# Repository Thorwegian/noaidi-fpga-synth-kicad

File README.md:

# Noaidi FPGA Synth: the board

The KiCad project for the Noaidi synthesizer's circuit board, in
progress. The gateware and firmware that run on it live in
[Thorwegian/noaidi-fpga-synth](https://github.com/Thorwegian/noaidi-fpga-synth),
and the synth itself is presented at [thj.no/synth](https://thj.no/synth/).

## What is on it

The perfboard prototype the board is based on. The board is a carrier for
two off-the-shelf modules and the few parts around them:

- **Tang Nano 20K** (U2) on headers: the sound engine.
- **ESP32-S3-DevKitC** (U1) on headers: MIDI, voices, patches and the
  console. The prototype runs an ESP32-C3 Super Mini; the board moves to
  the S3 (the firmware port is tracked in the synth repository,
  `docs/esp32s3_hw678.md`).
- **Two DIN MIDI inputs** (J1, J2) through 6N138 optocouplers (U3, U4):
  one for the keyboard, one for the dev host.
- **Audio out**: an Adafruit PCM510x I2S DAC module (U5) for analog, two
  RCA sockets (J3, J4) for S/PDIF.
- **USB-C** (J9) for power, into each module's 5 V rail through an
  LM66100 ideal diode (U6, U7), and the data pair to the ESP32.
- Pin headers for the second SPI bus, two I2C buses, UART0, I2S and
  S/PDIF, and 29 test points.

Two layers, 130.85 × 121.25 mm, through-hole apart from the two LM66100
(SC-70) and the ferrite bead.

## Layout

Front copper and silkscreen:

Back copper, mirrored:

The connector and module bodies render as footprints only: their 3D
models are not part of the project.

## Schematic

[pcb-schematic.pdf](https://thj.no/synth/images/pcb-schematic.pdf), all
five sheets: the root, `esp32`, `tang_nano_20k`, `usb` and `test_points`.

## Files

The root folder holds the KiCad project, this README and the licence.
Scripts go in `scripts/`, documents in `docs/`.

- `noaidi-fpga-synth.kicad_pro`, `.kicad_sch` and the four sheet files,
  `.kicad_pcb`, `.kicad_dru`
- `noaidi-fpga-synth.kicad_sym` and `noaidi-fpga-synth.pretty/`: the
  project's own symbols and footprints (the two modules, the DAC, the
  DIN sockets, the RCA and USB-C connectors)
- `scripts/render.sh`: regenerates the images above into `build/` with
  `kicad-cli` (KiCad 10); `scripts/crop.py` trims the 3D renders to the
  board
- `docs/requirements.md`: what the board has to do; the schematic and
  the layout are checked against it.
- `docs/esp32s3_hw678.md`: what the two HW-678 copies of the
  ESP32-S3-DevKitC-1 are, measured: the pins the module takes, the
  free pins, the USB bridge and the open USB-OTG pads, and the header
  pins read from two photos of the board, `docs/esp32s3_hw678_top.jpg`
  and `docs/esp32s3_hw678_bottom.jpg`. The synth repository's file with
  the Header pins section added.
- `docs/thirdparty/`: the vendors' documents the board is drawn from.
  Mechanical: the Tang Nano 20K's dimension drawing (`.pdf`, `.dxf`) and
  3D model (`.step`), and the Adafruit PCM510x's fab print with its
  dimensions. Electrical: the Tang Nano 20K's schematic and pinout, the
  GW2AR data sheet, the ESP32-S3-DevKitC-1 user guide, pinouts and
  schematic (v1.1), the
  Adafruit PCM510x guide and schematic, the 6N138 MIDI input circuit and
  the TOTX1950A optical transmitter's data sheet. The board's own parts,
  from the links in the schematic's Datasheet fields: the LM66100 ideal
  diode (U6, U7), the 6N138 optocoupler (U3, U4), the Lumberg 0105 DIN
  socket (J1, J2), the Kycon KLPX RCA socket (J3, J4) and the GCT
  USB4085 USB-C receptacle (J9; specification and drawing).

## Build tools

`kicad-cli` (KiCad 10) and `pdfunite` (poppler-utils) come from the
system's packages. The Python tools are listed in
`scripts/requirements.txt` and live in a virtual environment, `.venv/`
at the root, which is not committed:

    python3 -m venv .venv
    .venv/bin/pip install -r scripts/requirements.txt
    source .venv/bin/activate

- `skidl`: circuits described in Python. It is not in Ubuntu's packages.
  It finds KiCad's symbol libraries through the environment variable
  `KICAD10_SYMBOL_DIR` (`/usr/share/kicad/symbols` on Ubuntu).
- `pillow`: for `scripts/crop.py`.

Copyright © 2026 Thor H. Linløkken <thj@thj.no>
License: [CERN-OHL-S v2](LICENSE.txt)

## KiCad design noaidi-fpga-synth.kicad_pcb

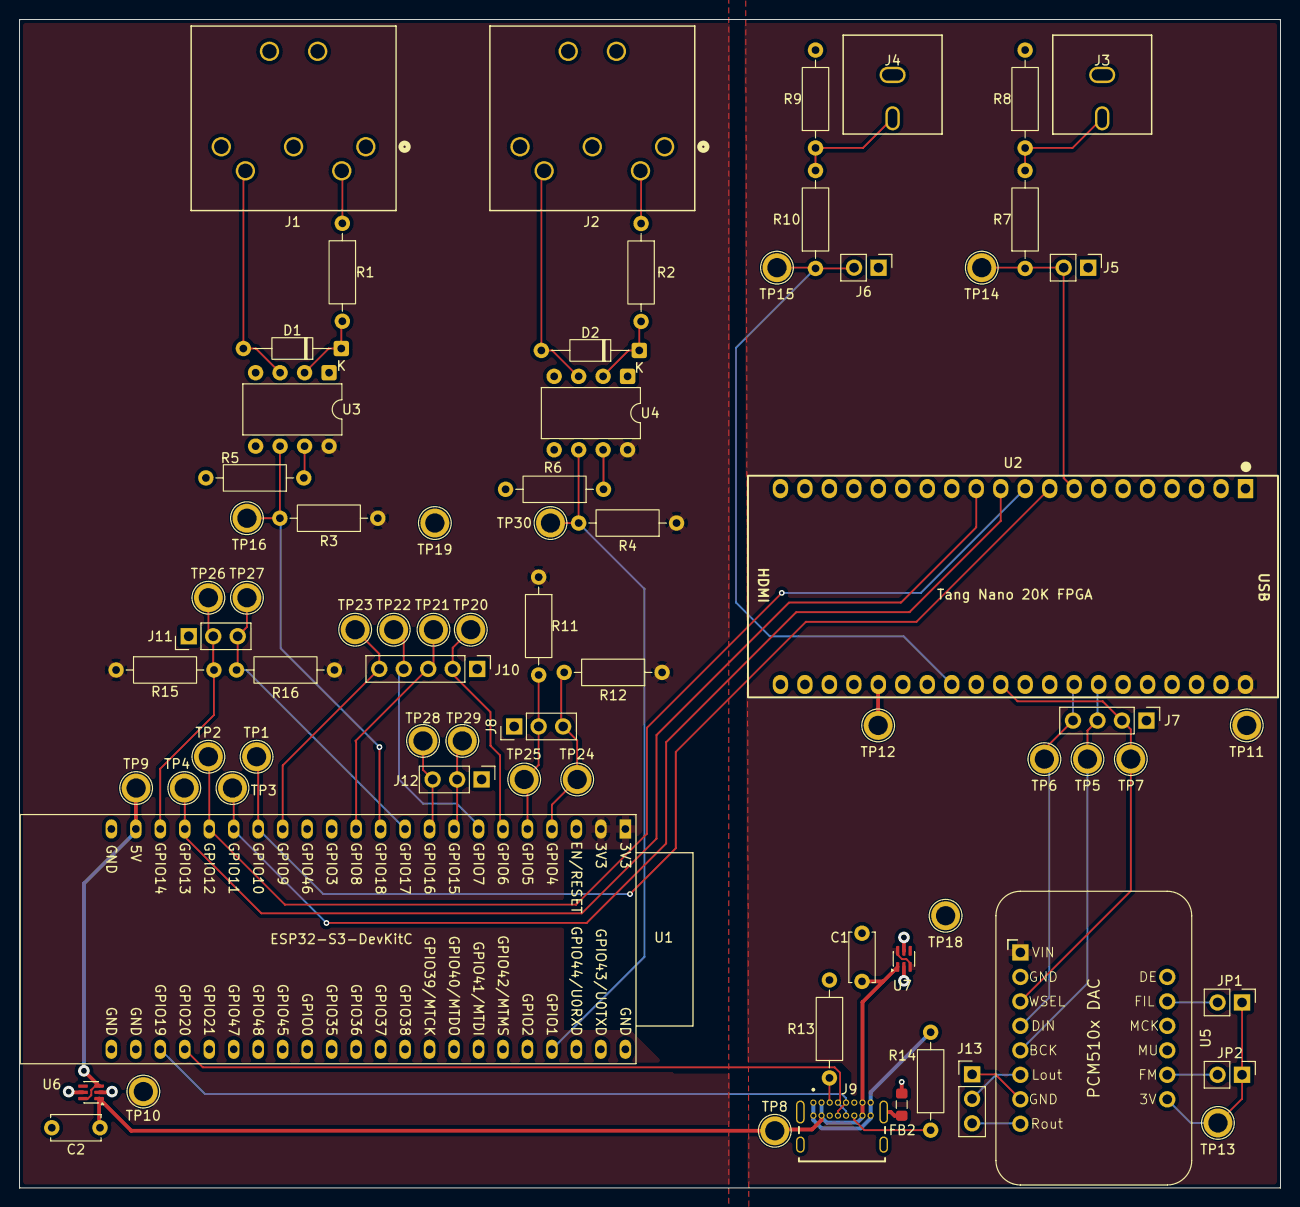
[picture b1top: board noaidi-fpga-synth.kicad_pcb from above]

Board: 2 copper layers, 130.8 x 121.2 mm, 72 parts (0 on the bottom side), 48 nets.

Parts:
C1, C2: 1u; C_Disc_D5.0mm_W2.5mm_P5.00mm
D1, D2: D; D_DO-35_SOD27_P10.16mm_Horizontal
FB2: FerriteBead; L_0805_2012Metric_Pad1.05x1.20mm_HandSolder
J1, J2: DIN-5_180degree; Lumberg_0105_05
J3, J4: Conn_Coaxial; RCA_Kycon_KLPX-0848A
J5, J6: Conn_01x02_Pin; PinHeader_1x02_P2.54mm_Vertical
J7: Conn_01x04_Pin; PinHeader_1x04_P2.54mm_Vertical
J8, J11, J12, J13: Conn_01x03_Pin; PinHeader_1x03_P2.54mm_Vertical
J9: USB_C_Receptacle_USB2.0_16P; GCT_USB4085-GF-A_REVB
J10: Conn_01x05_Pin; PinHeader_1x05_P2.54mm_Vertical
JP1, JP2: Jumper_2_Open; PinHeader_1x02_P2.54mm_Vertical
R1, R2, R3, R4, R7, R10: 220; R_Axial_DIN0207_L6.3mm_D2.5mm_P10.16mm_Horizontal
R5, R6, R11, R12, R15, R16: 4.7k; R_Axial_DIN0207_L6.3mm_D2.5mm_P10.16mm_Horizontal
R8, R9: 120; R_Axial_DIN0207_L6.3mm_D2.5mm_P10.16mm_Horizontal
R13, R14: 5.1k; R_Axial_DIN0207_L6.3mm_D2.5mm_P10.16mm_Horizontal
TP1, TP2, TP3, TP4, TP5, TP6, TP7, TP8, TP9, TP10, TP11, TP12, TP13, TP14, TP15, TP16, TP18, TP19, TP20, TP21, TP22, TP23, TP24, TP25, TP26, TP27, TP28, TP29, TP30: TestPoint; TestPoint_Plated_Hole_D2.0mm
U1: ESP32-S3-DevKitC
U2: Tang_Nano_20K; DIP-40_TangNano20K
U3, U4: 6N138; DIP-8_W7.62mm
U5: Adafruit_PCM510x
U6, U7: LM66100DCK; SOT-363_SC-70-6

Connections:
ESP_3V3: R3.1, R4.1, R11.1, R12.1, R15.1, R16.1, TP10.1 (1_1), U1.1 (3V3), U1.2 (3V3), U3.8 (VCC), U4.8 (VCC)
ESP_5V: TP9.1 (1_1), U1.21 (5V), U6.3 (~CE), U6.6 (VOUT)
ESP_UART0_RX: J12.3, TP28.1 (1_1), U1.9 (GPIO16/ADC2_CH5/32K_N)
ESP_UART0_TX: J12.2, TP29.1 (1_1), U1.8 (GPIO15/ADC2_CH4/32K_P)
ESP_UART1_RX: R3.2, TP16.1 (1_1), U1.11 (GPIO18/ADC2_CH7), U3.6 (VO2)
ESP_UART2_RX: R4.2, TP30.1 (1_1), U1.41 (GPIO1/ADC1_CH0), U4.6 (VO2)
EXT_5V: C1.1, C2.1, J9.A4 (VBUS), J9.A9 (VBUS), J9.B4 (VBUS), J9.B9 (VBUS), TP8.1 (1_1), U6.1 (VIN), U7.1 (VIN)
GND: C1.2, C2.2, FB2.2, J3.2 (Ext), J4.2 (Ext), J5.1, J6.1, J7.1, J8.1, J9.A1 (GND), J9.A12 (GND), J9.B1 (GND), J9.B12 (GND), J10.1, J11.1, J12.1, R5.2, R6.2, R8.2, R9.2, R13.2, R14.2, TP18.1 (1_1), TP19.1 (1_1), U1.22 (GND), U1.23 (GND), U1.24 (GND), U1.44 (GND), U2.20 (GND), U2.26 (GND), U2.39 (GND), U3.5 (GND), U4.5 (GND), U5.2 (GND), U6.2 (GND), U6.5 (ST), U7.2 (GND), U7.5 (ST)
I2C0_SCL: J8.3, R12.2, TP24.1 (1_1), U1.4 (GPIO4/ADC1_CH3)
I2C0_SDA: J8.2, R11.2, TP25.1 (1_1), U1.5 (GPIO5/ADC1_CH4)
I2C1_SCL: J11.2, R15.2, TP26.1 (1_1), U1.20 (GPIO14/ADC2_CH3)
I2C1_SDA: J11.3, R16.2, TP27.1 (1_1), U1.10 (GPIO17/ADC2_CH6)
I2S_BCK: J7.3, TP5.1 (1_1), U2.34 (56_IOR36A), U5.5 (BCK)
I2S_DATA: J7.4, TP6.1 (1_1), U2.33 (54_IOR38A), U5.4 (DIN)
I2S_WS: J7.2, TP7.1 (1_1), U2.30 (55_IOR36B), U5.3 (WSEL)
NANO_3V3: TP12.1 (1_1), U2.25 (3V3)
NANO_5V: TP11.1 (1_1), U2.40 (5V), U5.1 (VIN), U7.3 (~CE), U7.6 (VOUT)
unnamed: D1.2 (A), J1.5, U3.3 (C2)
unnamed: D1.1 (K), R1.2, U3.2 (C1)
unnamed: D2.2 (A), J2.5, U4.3 (C2)
unnamed: D2.1 (K), R2.2, U4.2 (C1)
unnamed: FB2.1, J9.S1 (SHIELD), J9.S2 (SHIELD), J9.S3 (SHIELD), J9.S4 (SHIELD)
unnamed: J1.4, R1.1
unnamed: J2.4, R2.1
unnamed: J3.1 (In), R7.2, R8.1
unnamed: J4.1 (In), R9.1, R10.2
unnamed: J9.A5 (CC1), R13.1
unnamed: J9.B5 (CC2), R14.1
unnamed: J13.1, U5.7 (G)
unnamed: J13.2, U5.6 (Lout)
unnamed: J13.3, U5.8 (Rout)
unnamed: JP1.2 (B), U5.13 (FIL)
unnamed: JP2.2 (B), U5.10 (FM)
unnamed: R5.1, U3.7 (VO1)
unnamed: R6.1, U4.7 (VO1)
PCM_3V3: JP1.1 (A), JP2.1 (A), TP13.1 (1_1), U5.9 (3V)
SPDIF0: J5.2, R7.1, TP14.1 (1_1), U2.8 (27_IOB8A)
SPDIF1: J6.2, R10.1, TP15.1 (1_1), U2.28 (86_IOT4A)
SPI2_CS_N: TP1.1 (1_1), U1.16 (GPIO10/ADC1_CH9), U2.9 (28_IOB8B)
SPI2_MISO: TP4.1 (1_1), U1.19 (GPIO13/ADC2_CH2), U2.12 (29_IOB14A)
SPI2_MOSI: TP3.1 (1_1), U1.17 (GPIO11/ADC2_CH0), U2.11 (26_IOB6B)
SPI2_SCLK: TP2.1 (1_1), U1.18 (GPIO12/ADC2_CH1), U2.10 (25_IOB6A)
SPI3_CS_N: J10.2, TP20.1 (1_1), U1.6 (GPIO6/ADC1_CH5)
SPI3_MISO: J10.5, TP23.1 (1_1), U1.15 (GPIO9/ADC1_CH8)
SPI3_MOSI: J10.4, TP22.1 (1_1), U1.7 (GPIO7/ADC1_CH6)
SPI3_SCLK: J10.3, TP21.1 (1_1), U1.12 (GPIO8/ADC1_CH7)
USB_D+: J9.A6 (D+), J9.B6 (D+), U1.26 (GPIO20/USB_D+)
USB_D-: J9.A7 (D-), J9.B7 (D-), U1.25 (GPIO19/USB_D-)
